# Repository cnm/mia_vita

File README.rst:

HOW TO BUILD MIA_VITA PROJECT
-----------------------------

*There is a very usefull Makefile at the top dir*

To compile the miavita project do this:

   - First download it from github
      $ git clone "https://github.com/cnm/mia_vita"

      (or if you are a developer)
      $ git clone "git@github.com:cnm/mia_vita"

   - Update the submodule (only necessary to run once)
      $ make init_git_submodules

   - Compile the ts7500_kernel ()
      $ make kernel

   - Compile all the code (except the kernel)
      $ make all

   - Install everything needed to the sdcard except the kernel

Overall help
------------

File Structure
==============

This is the file structure::

    .
    clean               - Directory for cleaning up the TS-7500 debian partition
    crosstool           - Crosstools binaries to compile for ARM
    documentation       - Documentation
    fred_framework      -
    interruption        - Module to treat the two interruptions
    kernel_sender       - Fred module which sends packets
    old_stuff           - Just for historical purposes. Should be deleted soon.
    rt2501              - Module changed to do the synchronization
    rt3070              - Module rt3070 for the wireless devices. It has not be changed.
    syscall             - Simple syscall to access the time set by the GPS
    timestamp-module    -
    ts7500ctl           - Binary of the ts7500ctl not changed. Just usefull to test big banging.
    ts7500_kernel       - Modified kernel for working in the TS7500

How to pull the git sub modules
===============================

* Pull the main module:
$> git clone "git@github.com:cnm/mia_vita.git"

* Optional check the status
$> git submodule status

* First add the submodule repository URLs to .git/config by running:
$> git submodule init

* Update the submodules
$> git submodules update

Development Username and password
=================================

*Arm devices*:

* Username: root
* Password: cnm

*Laptop*:

* Username: miavita
* password: inesc-id

FIRST STEPS - Connect to the RT7750 with serial cable
=====================================================

* Install minicom
* Run sudo minicom -s
* Set in Serial Port Setup

  * Serial Device: /dev/ttyUSB0 (or /dev/ttyUSB1)

  * Bps: 115200 8N1

  * Hardware Flow Control: No

Documentation URLs
==================
In here put the cites with documentation for the little arms:

* http://tech.groups.yahoo.com/group/ts-7000/

Sites to discover what chipset is in what wireless card

* http://wireless.kernel.org/en/users/Drivers/
* http://linux-wless.passys.nl/

Filesystem and kernels
======================
http://tagus.inesc-id.pt/~jtrindade/mia_vita/

Stable image is at:

http://tagus.inesc-id.pt/~jtrindade/mia_vita/block_images/mia_vita_image_stable

Establishing AD-HOC Communication (On the OLD devices with rt2050)
===================================================================

PC1 - LGs laptops from INESC
PC2 - TS-7550s

Run in PC1
##########
* ifconfig eth1 down
* ifconfig eth1 up
* iwconfig eth1 essid teste mode Ad-Hoc channel 1 ap 02:0c:f1:b5:8f:01 key off
* ifconfig eth1 192.168.0.1

Run in PC2
#########
* Edit the file /etc/modprobe.d/blacklist and add rt73usb
* Copy the file "rt73_ts7500.ko" to "/lib/modules/2.6.24.4/kernel/drivers/net/wireless/rt2x00". You may find the rt_ts7500.ko file in this zip file: "ftp://ftp.embeddedarm.com/ts-arm-sbc/ts-7500-linux/binaries/wifi-g-usb-2_rt2501usb-binaries.tar.gz"
* Run depmod -a
* Restart (don't really now if it is necessary)
* ifconfig rausbwifi up
* iwconfig rausbwifi essid teste mode Ad-Hoc channel 1 ap 02:0C:F1:B5:CC:5D key off
* ifconfig rausbwifi 192.168.0.25

Autostart interfaces in the TS7550
##################################
I added the following lines to /etc/network/interfaces:

auto rausbwifi
iface rausbwifi inet static
    address 192.168.0.25
    netmask 255.255.255.0
    pre-up /root/adhoc.sh

Note that the /root/adhoc.sh is a script with the previous instructions (don't forget to markit executable)

Placa Wireless IOGEAR (Can't make it work in adhoc)
====================================================

*Modulos:*
zd1211 -> Old module developed by the company (available in sourceforge)
zd1211rw -> New module developed by the community (available since 2.6.18-rc1)

*Referencias:*
Site of the module:
http://wiki.debian.org/zd1211rw

Site to compile the module + arguments of the iwconfig:
https://docs.google.com/viewer?url=http://www.linuxowl.com/ffs/DocsSoftware/SWMULZ-5400-Linux-UserGuide.pdf

Automatically boot into Debian linux
====================================
In linux initrd (busybox) in the root directory issue:

rm linuxrc; ln -sf linuxrc-sdroot linuxrc; save

Boot from sdcard via hardware
=============================

Connect pin 7 to GND

Changes done in the Operating System
====================================

Fix the name of the wireless card
---------------------------------
Add the file "01-our-rewrite.rules" to /etc/udev.d/rules with the following text:

   # All ralink wireless are named rausbwifi
   SUBSYSTEM=="net", ACTION=="add", KERNEL=="ra*", NAME="rausbwifi"

Blacklist the rt73 usb driver
-----------------------------
add "blacklist rt73usb" to /etc/modprobe.d/blacklist

Startup adhoc at the beggining
-------------------------------
In /etc/network/interfaces put:

    auto rausbwifi
    iface rausbwifi inet static
    address 192.168.0.3
    netmask 255.255.255.0
    pre-up /root/adhoc.sh rausbwifi 192.168.1.3

and /root/adhoc.sh should contain:

#!/bin/bash

    ifconfig $1 up
    iwconfig $1 mode managed
    sleep 3
    ifconfig $1 down
    ifconfig $1 up
    iwconfig $1 mode ad-hoc essid teste channel 1 ap 02:0C:F1:B5:CC:5D
    iwconfig $1 rate 1M
    ifconfig $1 $2

How to compile a user program in another machine for ts-7500
============================================================
* First setup the cross-compile. Download it from: ftp://ftp.embeddedarm.com/ts-arm-sbc/ts-7500-linux/cross-toolchains/crosstool-linux-gcc-4.2.1-glibc-2.7-oabi.tar.gz

* Untar it: tar xvzf crosstool-linux-gcc-4.2.1-glibc-2.7-oabi.tar.gz

* cd into usr/local/arm-oabi-toolchain/arm-unknown-linux-gnu/bin/

* Check if you have a broken link. In my case ``ls -l`` gives me this broken link: arm-unknown-linux-gnu-cc -> /usr/local/arm-oabi-toolchain/arm-unknown-linux-gnu/bin/arm-unknown-linux-gnu-gcc

* Fix it:

    $ rm arm-unknown-linux-gnu-cc

    $ ln -s \`pwd\`/arm-unknown-linux-gnu-gcc arm-unknown-linux-gnu-cc

* Now to compile programs for the ts-7500 just use ``arm-unknown-linux-gnu-gcc`` instead of ``gcc``

How to compile kernel for the TS-7500 node
==========================================

* Download the kernel from: ftp://ftp.embeddedarm.com/ts-arm-sbc/ts-7500-linux/sources/linux-2.6.24-ts-src-aug102009.tar.gz
 (or fetch it from: http://github.com/joninvski/ts_7500_kernel )

* Download the crosstool chain: ftp://ftp.embeddedarm.com/ts-arm-sbc/ts-7500-linux/cross-toolchains/crosstool-linux-gcc-4.2.1-glibc-2.7-oabi.tar.gz
 (or fetch it from: http://github.com/joninvski/arm-uclibc-3.4.6 )

* Download the module for the wireless card: ftp://ftp.embeddedarm.com/ts-arm-sbc/ts-7500-linux/sources/wifi-g-usb-2_rt2501usb-sources.tar.gz
 (or fetch it from: http://github.com/joninvski/USB_Wifi_RT2501_TS-7500 )

First compile the kernel
------------------------

* In the 2.6.24.4-cavium directory change the Makefile pointing it to the correct path. In my case:

  * CROSS_COMPILE   ?= /home/workspace/plaquinhas/kernel/arm-uclibc-3.4.6/bin/arm-linux-

* Put the crosstoll chain in the path

* Run: $> make ts7500_defconfig

* Run: $> make menuconfig
(If there is any error compiling menuconfig just install the package libncurses-dev)

* Go to networking and select all the modules necessary for iptables/netfilter
(The .config present in the git repository contains this information)

* Run: $> make modules; make modules_install
(in here i did a litlle trick: chmod a+w /lib/modules to be able to install modules whitout being root)

Copy the kernel to the sd card
------------------------------

* Put the sdcard in the computer (let's assume sdb)

* Run: dd if=arch/arm/boot/zImage of=/dev/sdb2\

* Mount /dev/sdb4

* Copy the modules present in /lib/modules/2.6.24.4/ to the card 4th partition (to the same directory)

Compile the usb wifi card driver
--------------------------------

* Go the the directory of the usb wifi source code.

* In the Makefile change the cross tools path and the target to 7500
(you can find these changes in the git repository)

* make

* Copy the ts73.ko file to the /lib/modules/2.6.24.4/kernel/drivers/net/wireless/rt2x00/rt73_ts7500.ko (note this is in the forth partition of the sd-card)o

* You should probably (not tested) run depmod on the arm node (then restart)

Run the kernel from the sd-card
-------------------------------

* Put the jumpers in the development board: JP1 = ON; JP2 = OFF

* Do a depmod -a to do all module dependencies

Copy the kernel and initrd to the flash in the arm
--------------------------------------------------

* On my pc (I cannot to this in the card) I copy the sdb2 and sdb3 partitions to two files and then use those files to copy to the flash. This is how to do it.

* Put the sd-card on the pc

* dd if=/dev/nbd2 of=/tmp/zImage
* dd if=/dev/nbd3 of=/tmp/initrd
* Copy both these files to the /dev/ndb4 file system (mount it!!!!!!)
* Unmount /dev/ndb4 after copy
* Put the sd-card on the arm and then turn it up
* Do:
 * spiflashctl -W 4095 -z 512 -k part1 -i /temp/zImage
 * spiflashctl -W 32 -z 65536 -k part2 -i /temp/initrd
 * sync

Add a batman service at startup
==============================
* update-rc.d batman-adv defaults

Udev rule
=========

On some linux distros users experience some minicom problems, while using the serial cable to connect to the development board. In other words, minicom stops working wtih an error message similar to::

   Unable to open /dev/ttyUSB0

This happens because the kernel keeps changing the device name and ttyUSB0 is now ttyUSB1. This can be avoided by creating an udev rule. The following udev rule is the simplest one, which provides a workaround to this problem:

* Open file /etc/udev/rules.d/99_serial_cable.rules
* Write: SUBSYSTEM=="usb", KERNEL=="ttyUSB*", NAME="ttyUSB0"

Or you can just copy and execute the command::

   sudo sh -c 'echo "SUBSYSTEM==\"usb\", KERNEL==\"ttyUSB*\", NAME=\"ttyUSB0\"" > /etc/udev/rules.d/99_serial_cable.rules'

You will need to restar udev or your pc.

Keep in mind that this rule is very simple and it only tells the udev layer to give the name ttyUSB0 to every device that the kernel reports as beginning with ttyUSB. If you ever need to connect two serial cables via USB adapters, you'll need to add another parameter to the rule above. To do this we first need the device ID for each usb adapter. Issue::

   lsusb

Which should give you an output similar to::

   Bus 005 Device 001: ID 1d6b:0001 Linux Foundation 1.1 root hub
   Bus 004 Device 002: ID 0b05:1712 ASUSTek Computer, Inc. BT-183 Bluetooth 2.0+EDR adapter
   Bus 004 Device 001: ID 1d6b:0001 Linux Foundation 1.1 root hub
   Bus 003 Device 002: ID 04f3:0210 Elan Microelectronics Corp. AM-400 Hama Optical Mouse

Now, what we're looking for is the device id, which is the second hexadecimal number in the ID field. For example, the blue tooth adapter has a device ID of 1712.

The udev rule for multiple adapters becomes::

   SUBSYSTEM=="usb", ATTR{idProduct}=="0001", NAME="ttyUSB0"
   SUBSYSTEM=="usb", ATTR{idProduct}=="0002", NAME="ttyUSB1"

The udev will give the name ttyUSB0 to the usb adapter with id 0001 and ttyUSB1 to the usb adapter with id 0002.

Compile spictl
==============

Erase the LD_FLAGS variable from the Makefile

Update the FPGA
===============

Get the new FPGA from::

    wget ftp://ftp.embeddedarm.com/ts-arm-sbc/ts-7500-linux/binaries/ts-bitstreams/ts7500_opencore-rev5-8XUART.vme.gz

Compile the ts7500ctl tool::

    wget ftp://ftp.embeddedarm.com/ts-arm-sbc/ts-7500-linux/sources/ts7500ctl.c
    wget ftp://ftp.embeddedarm.com/ts-arm-sbc/ts-7500-linux/sources/vmopcode.h
    wget ftp://ftp.embeddedarm.com/ts-arm-sbc/ts-7500-linux/sources/ispvm.c
    gcc -Wall -O -o ts7500ctl ts7500ctl.c ispvm.c

Load the new FPGA::

    ./ts7500ctl -l ts7500_opencore-rev5-8XUART.vme.gz

Test::

    arm3:~# ./spictl -l 1 -w 0B:00:20:00:00 -r 32 | hexdump -C
    00000000  20 94 e0 d4 30 03 e0 07  60 07 e0 64 00 08 e0 07  | ...0...`..d....|
    00000010  a0 03 e0 83 74 37 e0 a0  00 10 23 00 13 40 9f e4  |....t7....#..@..|

How to add a system call on arm
===============================

Adding a system call is not as straight forward as creating a kernel module. The issue is that the system call table is a static table that resides inside
the kernel. Therefore it cannot be modified dynamically. More specifically you can modify the table but it is impossible to extend it. As a result, adding
a system call requires recompiling the kernel itself.

First thing first, download the kernel sources for the ts7500 board. cd into the downloaded sources and lets begin.
Adding a system call can be done in four steps:

* Edit the file ``arch/arm/kernel/calls.S`` and add a ``CALL`` statement::

    CALL(sys_mycall)

  Note: The syscall will be called ``mycall``, but here it is necessary to
  prefix it with ``sys``. Another thing to consider is that the system call
  table size must be a multiple of 4. For example if it has 352 calls you
  need to add 4 more calls. Use ``CALL(sys_ni_syscall)`` to add dummy system
  calls. When you're finished take note of your system call number, in our
  case we added 4 calls and suppose that our call is the last one, its number
  will be 356.

* Edit the file ``include/asm/unistd.h`` and add a ``define`` statement to the ones already in there::

    #define __NR_mycall       (__NR_SYSCALL_BASE+356)

  Note: The define constant must be prefixed with ``__NR_`` and notice the
  number 356.

* Create your system call. You'll need to decide which folder to put your .c file. There are a lot of choices here - fd, ipc, drivers, etc. No matter where you decide to put it you'll need to change the Makefile in it to compile your file. Suppose your file is named ``mysyscall.c``, add ``mysyscall.o`` to one of the object targets in the Makefile. Make sure that target will run, that is, if that option is enabled in the kernel. The ``mysyscall.c`` file will look something like::

    #include <linux/linkage.h>
    #include <linux/kernel.h>

    asmlinkage int sys_mysyscall(void){
     printk(KERN_EMERG "MY SYSCALL\n");
     return 1;
    }

* Finally, edit the file ``include/linux/syscalls.h`` and add your call header::

    asmlinkage int sys_mysyscall(void);

Mac Addresses
=============

Ethernet
########

    MV-47 - 00:d0:69:43:3f:ce - 99

    MV-34 - 00:d0:69:43:3f:c0 - 109

    MV-58 - 00:d0:69:43:3f:b9 - 145

    MV-50 - 00:d0:69:43:3f:c7 - 138

    MV-49 - 00:d0:69:43:3f:b3 - 143

Wireless cards
##############

    MV-61 94:0c:6d:e1:85:e5

    MV-41 e0:cb:4e:a6:5a:be

    Simao 94:44:52:01:95:b3

Setting up kthread to send data
===============================

The kthread module resides inside ``kernel_sender`` folder and has several parameters which can be useful to configure it::

    # modinfo send_kthread.ko

    filename:       sender_kthread.ko
    description:    This module spawns a thread which reads the buffer exported by João ands sends samples accross the network.
    author:         Frederico Gonçalves, [frederico.lopes.goncalves@gmail.com]
    license:        GPL v2
    depends:        int_mod
    vermagic:       2.6.24.4 mod_unload ARMv4
    parm:           bind_ip:This is the ip which the kernel thread will bind to. Default is localhost. (charp)
    parm:           sink_ip:This is the sink ip. Default is localhost. (charp)
    parm:           sport:This is the UDP port which the sender thread will bind to. Default is 57843. (ushort)
    parm:           sink_port:This is the sink UDP port. Default is 57843. (ushort)
    parm:           node_id:This is the identifier of the node running this thread. Defaults to 0. (ushort)
    parm:           read_t:The sleep time for reading the buffer. (uint)

Every parameter has its own default value, but you'll probably want to specify ``bind_ip`` and ``sink_ip`` ::

    # insmod sender_kthread.ko bind-ip="172.20.41.138" sink-ip="172.20.41.123"

Don't forget to insert the ``int_mod.c`` module first and that's it. You'll just need to run the server program as ::

    # user/main

You can specify aditional parameters ::

    # user/main -h

    Usage: ./main [-i <interface>] [-p <listen_on_port>] [-b <output_binary_file>] [-j <output_json_file>]
    -i     Interface name on which the program will listen. Default is eth0
    -p     UDP port on which the program will listen. Default is 57843
    -b     Name of the binary file to where the data is going to be written. Default is miavita.bin
    -j     Name of the json file to where the data is going to be written. Default is miavita.json

Test Results (made by Simao)
============================

Check the following url:

http://tagus.inesc-id.pt/~spedro/MIA-VITA/

Test Image (made by Simao)
============================

This image should be used for all wireless tests from now on.

check the following url:
http://tagus.inesc-id.pt/~spedro/mia_vita_image_tests_0.1

Arms Embedded suggested this Wireless card with external antenna
================================================================

HAWNU1 Hi-Gain Wireless-150N USB Network Adapter w/Range Amplifi
http://www.gohawking.com/store/product_info.php?products_id=438&osCsid=valhhlsf19rnueqs8shgdgduk1

Compile for uCLIBC
==================

Use the crosstool/arm-uclibc-3.4.6/ not the crosstool/arm-unknown-linux-gnu/ crosstool

Ping broadcast in ADHOC
=======================

    echo "0" > /proc/sys/net/ipv4/icmp_echo_ignore_broadcasts

Change from 802.11N to 802.11B
===============================

Edit file:

    etc/Wireless/RT2870STA/RT2870STA.dat

and change WirelessMode=5 to WirelessMode=1

More info available at: http://ubuntuforums.org/showthread.php?t=1566572

    @> WirelessMode=value
        0: legacy 11b/g mixed
        1: legacy 11B only
        2: legacy 11A only //Not support in RfIcType=1(id=RFIC_5225) and RfIcType=2(id=RFIC_5325)
        3: legacy 11a/b/g mixed //Not support in RfIcType=1(id=RFIC_5225) and RfIcType=2(id=RFIC_5325)
        4: legacy 11G only
        5: 11ABGN mixed
        6: 11N only
        7: 11GN mixed
        8: 11AN mixed
        9: 11BGN mixed
        10: 11AGN mixed

Some test commands
==================

Commands ::

   insmod int_mod.ko
   insmod sender_kthread.ko bind-ip="192.168.2.45" sink-ip="192.168.2.47" node-id="5"
   ./receiver -i bat0 -j /tmp/manel/miavita.json -z /tmp/manel/miavita.json.archive

================================

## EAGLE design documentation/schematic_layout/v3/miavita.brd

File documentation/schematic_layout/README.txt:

FILE *.brd -> Circuit Board layout
FILE *.sch -> Circuit Schematic

IMPORTANT:
The pdf's exports sould be done in a way so they face each other.

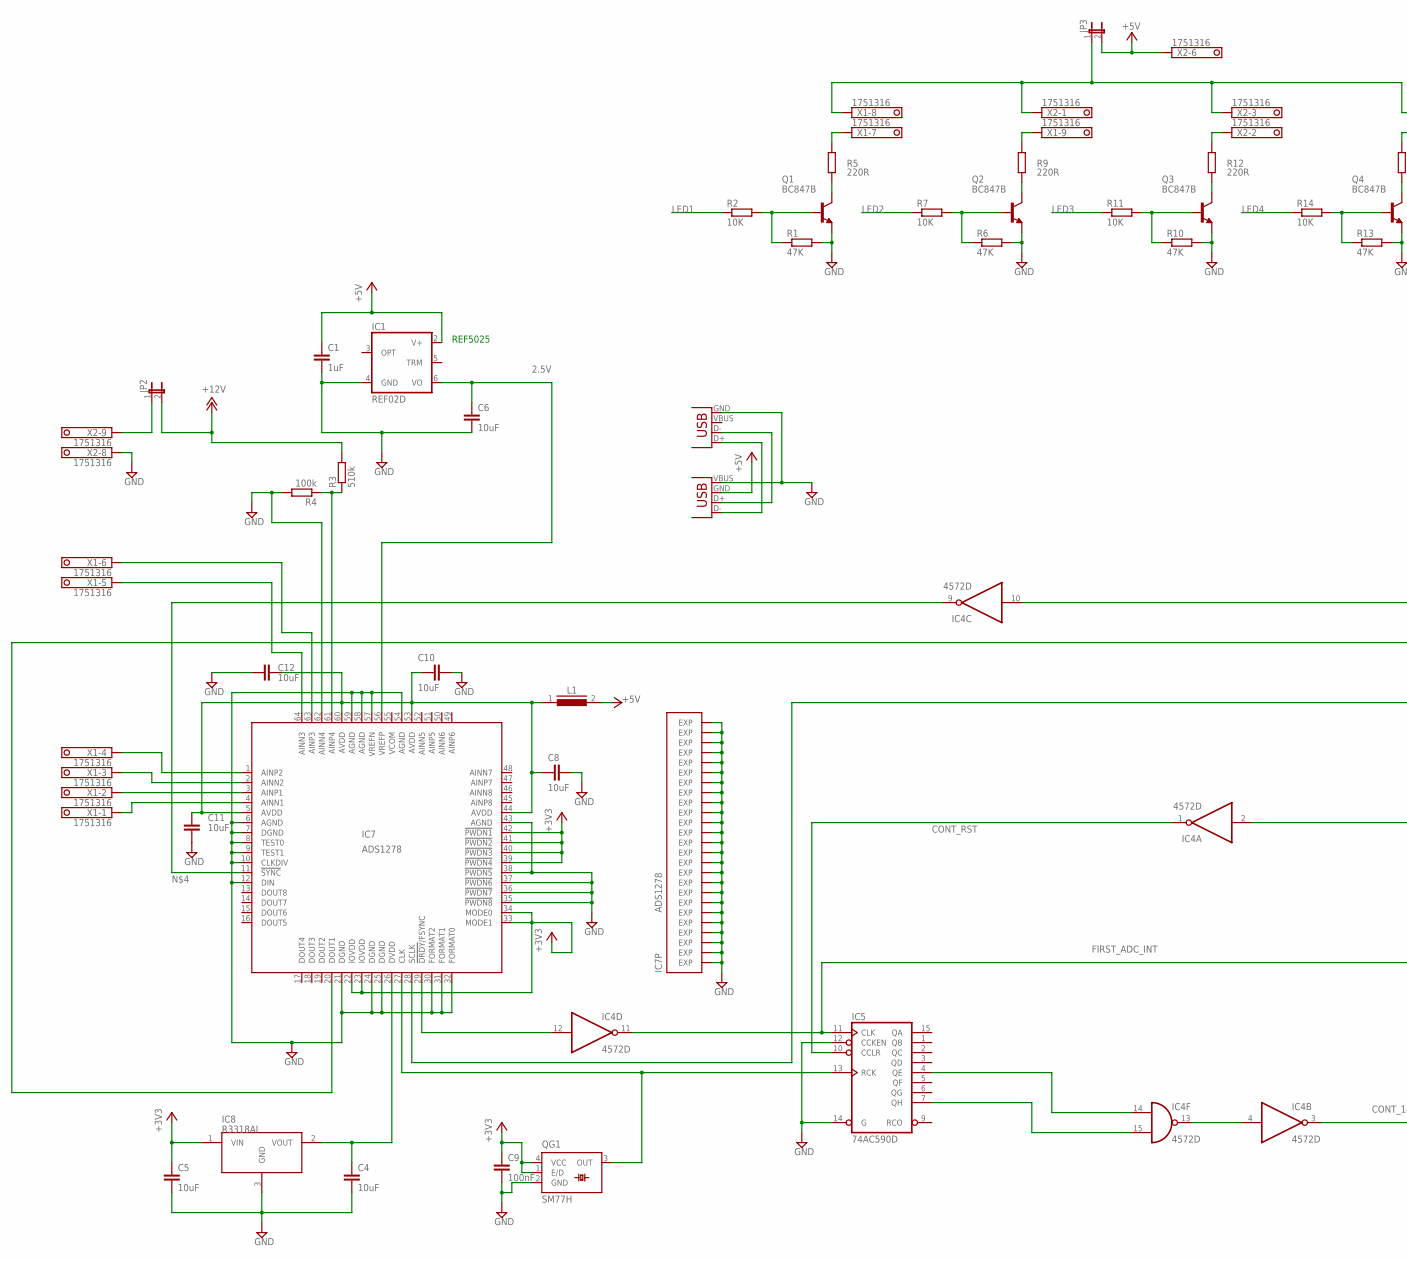
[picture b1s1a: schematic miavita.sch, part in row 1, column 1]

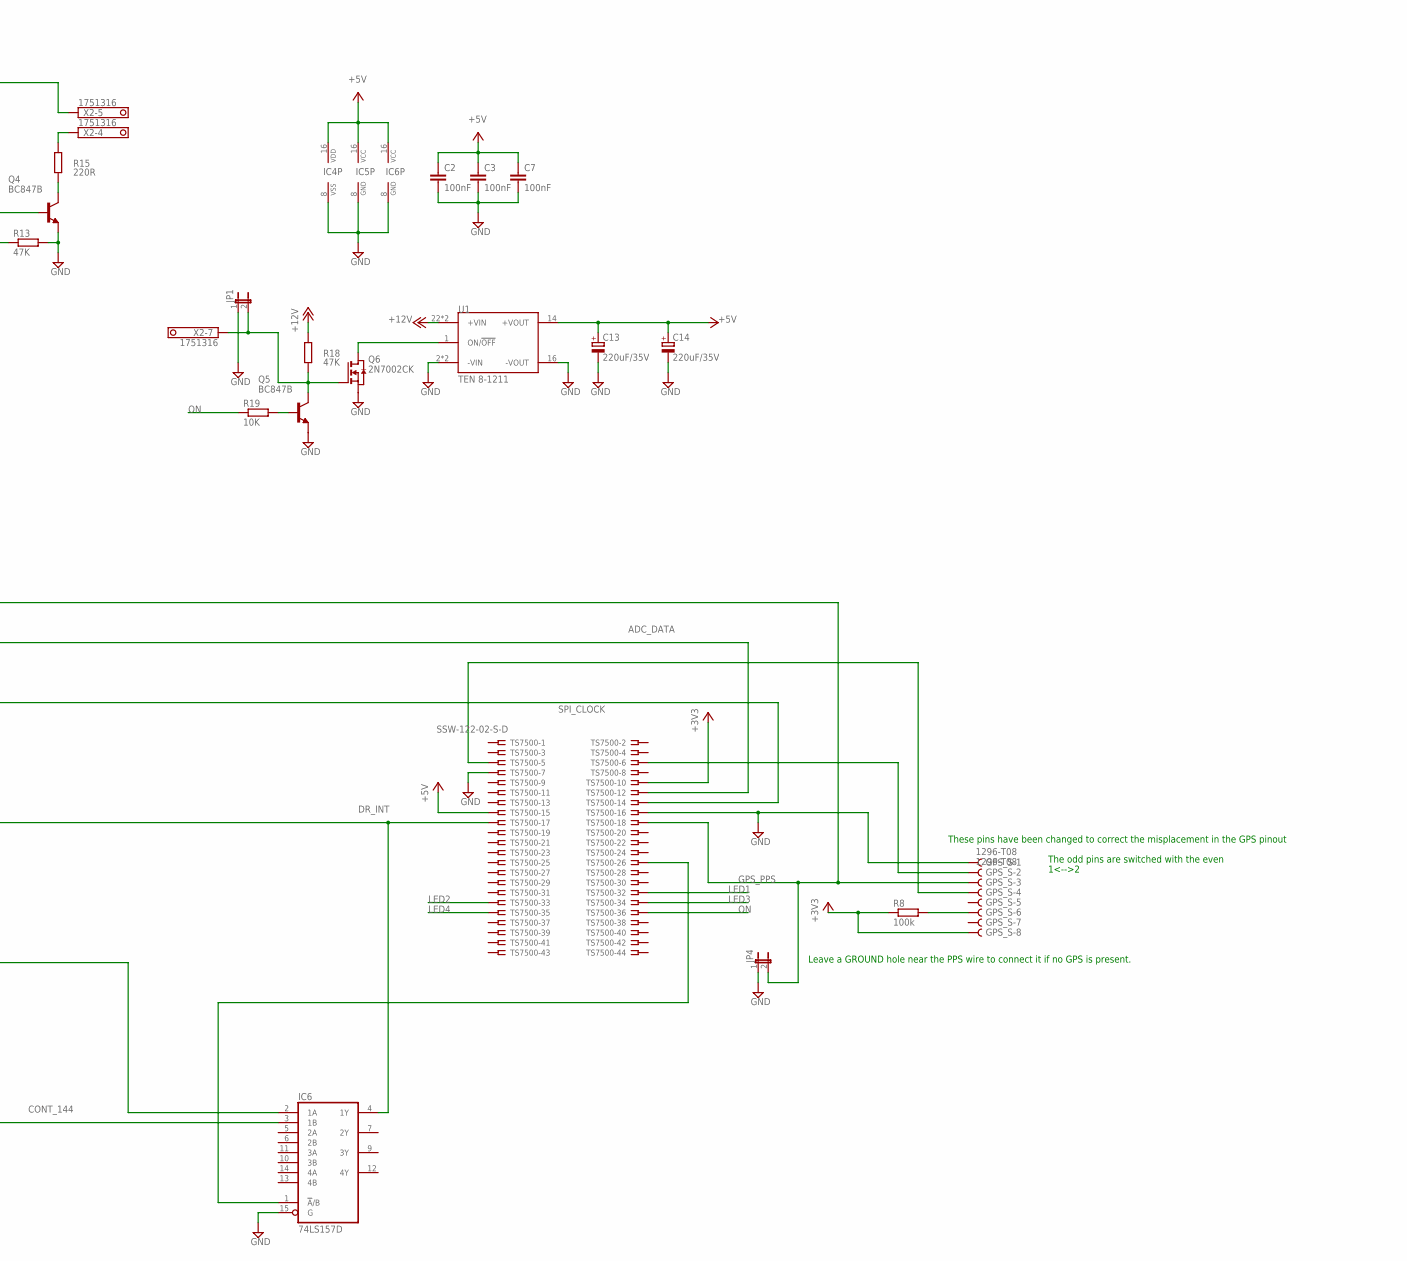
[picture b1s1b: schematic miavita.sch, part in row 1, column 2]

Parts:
C1: 1uF; C0603
C2, C3, C7, C9: 100nF; C0603
C4, C5, C6: 10uF; C1210
C8, C10, C11, C12: 10uF; C0805
C13, C14: 220uF/35V; UD-10X10_NICHICON
GPS_S: 1296-T08; 1296-08
IC1: REF02D; SO08
IC4: 4572D; SO16
IC5: 74AC590D; SO16
IC6: 74LS157D; SO16
IC7: ADS1278; HTQFP-64-PAP
IC8: R3318AI; SOT23
JP1, JP2, JP3, JP4: JP1E; JP1
L1: FAIR-RITE_2506031027Y0; L0603
Q1, Q2, Q3, Q4, Q5: BC847B; SOT23
Q6: 2N7002CK; SOT23
QG1: SM77H
R1, R6, R10, R13, R18: 47K; R0603
R2, R7, R11, R14, R19: 10K; R0603
R3: 510k; R0603
R4, R8: 100k; R0603
R5, R9, R12, R15: 220R; R0603
TS7500: SSW-122-02-S-D
U1: TEN 8-1211; TRACOPOWER_TEN-8-SERIES
USBA: USB-A-H
USBB: USBPTH; USB-B-PTH
X1, X2: 1751316

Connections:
2.5V: C6.1, IC1.6 (VO), IC7.56 (VREFP)
+1V8: C4.1, IC7.26 (DVDD), IC8.2 (VOUT)
+3V3: C5.1, C9.1, GPS_S.8, IC7.22 (IOVDD), IC7.23 (IOVDD), IC7.33 (MODE1), IC7.34 (MODE0), IC7.39 (!PWDN4), IC7.40 (!PWDN3), IC7.41 (!PWDN2), IC7.42 (!PWDN1), IC8.1 (VIN), QG1.1 (E/D), QG1.4 (VCC), R8.1, TS7500.10
+5V: C1.1, C2.1, C3.1, C7.1, C13.+, C14.+, IC1.2 (V+), IC4.16 (VDD), IC5.16 (VCC), IC6.16 (VCC), JP3.2, L1.2, TS7500.15, U1.14 (+VOUT), USBA.GND (VBUS), X2.6
+12V: JP2.2, R3.2, R18.1, U1.22 (+VIN), U1.23 (+VIN)
ADC_DATA: IC7.20 (DOUT1), TS7500.12
CONT_144: IC4.3 (O), IC6.3 (1B)
CONT_RST: IC4.1 (O), IC5.10 (CCLR)
DR_INT: IC4.2 (I), IC6.4 (1Y), TS7500.17
FIRST_ADC_INT: IC4.11 (O), IC5.11 (CLK), IC6.2 (1A)
GND: C1.2, C2.2, C3.2, C4.2, C5.2, C6.2, C7.2, C8.2, C9.2, C10.2, C11.2, C12.2, C13.-, C14.-, GPS_S.1, IC1.4 (GND), IC4.8 (VSS), IC5.8 (GND), IC5.12 (CCKEN), IC5.14 (G), IC6.8 (GND), IC6.15 (G), IC7.6 (AGND), IC7.7 (DGND), IC7.8 (TEST0), IC7.9 (TEST1), IC7.10 (CLKDIV), IC7.12 (DIN), IC7.21 (DGND), IC7.24 (DGND), IC7.25 (DGND), IC7.30 (FORMAT2), IC7.31 (FORMAT1), IC7.32 (FORMAT0), IC7.35 (!PWDN8), IC7.36 (!PWDN7), IC7.37 (!PWDN6), IC7.38 (!PWDN5), IC7.43 (AGND), IC7.54 (AGND), IC7.57 (VREFN), IC7.58 (AGND), IC7.59 (AGND), IC7.62 (AINN4), IC7.EXP1 (EXP), IC7.EXP2 (EXP), IC7.EXP3 (EXP), IC7.EXP4 (EXP), IC7.EXP5 (EXP), IC7.EXP6 (EXP), IC7.EXP7 (EXP), IC7.EXP8 (EXP), IC7.EXP9 (EXP), IC7.EXP10 (EXP), IC7.EXP11 (EXP), IC7.EXP12 (EXP), IC7.EXP13 (EXP), IC7.EXP14 (EXP), IC7.EXP15 (EXP), IC7.EXP16 (EXP), IC7.EXP17 (EXP), IC7.EXP18 (EXP), IC7.EXP19 (EXP), IC7.EXP20 (EXP), IC7.EXP21 (EXP), IC7.EXP22 (EXP), IC7.EXP23 (EXP), IC7.EXP24 (EXP), IC7.EXP25 (EXP), IC8.3 (GND), JP1.1, JP4.1, Q1.2 (E), Q2.2 (E), Q3.2 (E), Q4.2 (E), Q5.2 (E), Q6.2 (S), QG1.2 (GND), R1.2, R4.2, R6.2, R10.2, R13.2, TS7500.7, TS7500.16, U1.2 (-VIN), U1.3 (-VIN), U1.16 (-VOUT), USBA.VBUS (GND), USBB.GND, X2.8
GPS_PPS: GPS_S.3, IC4.10 (I), JP4.2, TS7500.18
LED1: R2.1, TS7500.32
LED2: R7.1, TS7500.33
LED3: R11.1, TS7500.34
LED4: R14.1, TS7500.35
unnamed: IC6.1 (!A!/B), TS7500.26
unnamed: IC4.15 (I1), IC5.7 (QH)
unnamed: IC4.14 (I0), IC5.4 (QE)
unnamed: IC4.9 (O), IC7.11 (!SYNC)
unnamed: IC4.4 (I), IC4.13 (O)
unnamed: IC4.12 (I), IC7.29 (!DRDY!/FSYNC)
unnamed: IC7.3 (AINP1), X1.2
unnamed: Q5.1 (B), R19.2
unnamed: IC7.4 (AINN1), X1.1
unnamed: IC7.1 (AINP2), X1.4
unnamed: IC7.61 (AINP4), R3.1, R4.1
unnamed: USBA.D+ (D-), USBB.D-
unnamed: IC7.63 (AINP3), X1.6
unnamed: Q2.1 (B), R6.1, R7.2
unnamed: Q2.3 (C), R9.1
unnamed: IC5.13 (RCK), IC7.27 (CLK), QG1.3 (OUT)
unnamed: USBA.D- (D+), USBB.D+
unnamed: C8.1, C10.1, C11.1, C12.1, IC7.5 (AVDD), IC7.44 (AVDD), IC7.53 (AVDD), IC7.60 (AVDD), L1.1
unnamed: R9.2, X1.9
unnamed: Q3.1 (B), R10.1, R11.2
unnamed: Q3.3 (C), R12.1
unnamed: R12.2, X2.2
unnamed: Q4.1 (B), R13.1, R14.2
unnamed: Q4.3 (C), R15.1
unnamed: R15.2, X2.4
unnamed: JP2.1, X2.9
unnamed: JP3.1, X1.8, X2.1, X2.3, X2.5
unnamed: IC7.2 (AINN2), X1.3
unnamed: JP1.2, Q5.3 (C), Q6.1 (G), R18.2, X2.7
unnamed: Q6.3 (D), U1.1 (ON/!OFF)
unnamed: IC7.64 (AINN3), X1.5
unnamed: Q1.3 (C), R5.1
unnamed: Q1.1 (B), R1.1, R2.2
unnamed: R5.2, X1.7
unnamed: GPS_S.2, TS7500.6
unnamed: GPS_S.4, TS7500.5
unnamed: GPS_S.6, R8.2
ON: R19.1, TS7500.36
SPI_CLOCK: IC7.28 (SCLK), TS7500.14

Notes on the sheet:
Leave a GROUND hole near the PPS wire to connect it if no GPS is present.
REF5025
These pins have been changed to correct the misplacement in the GPS pinout
The odd pins are switched with the even
1<-->2

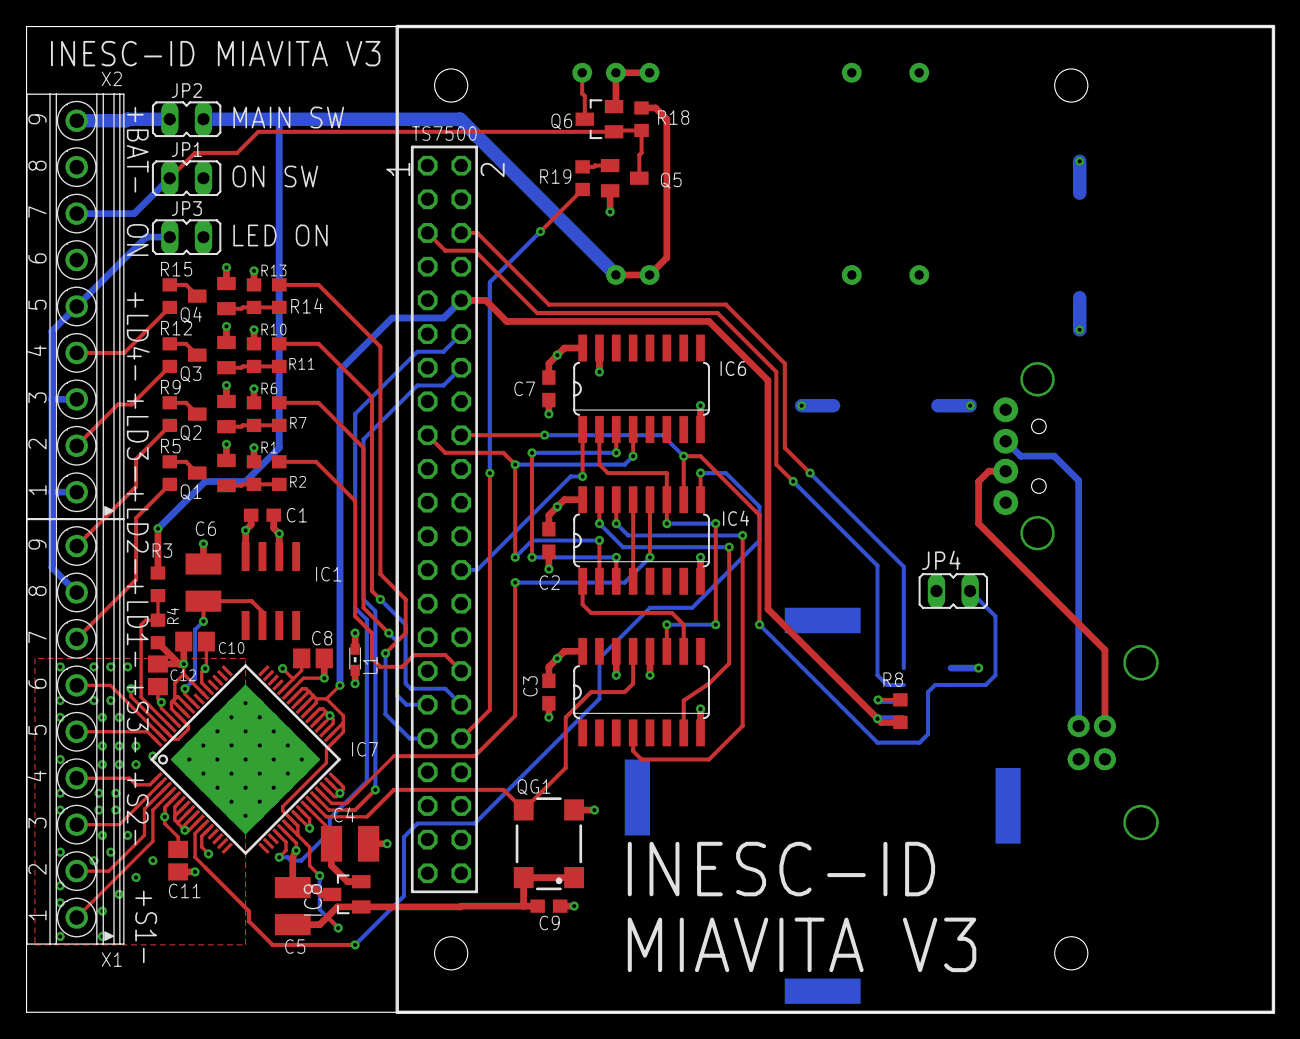
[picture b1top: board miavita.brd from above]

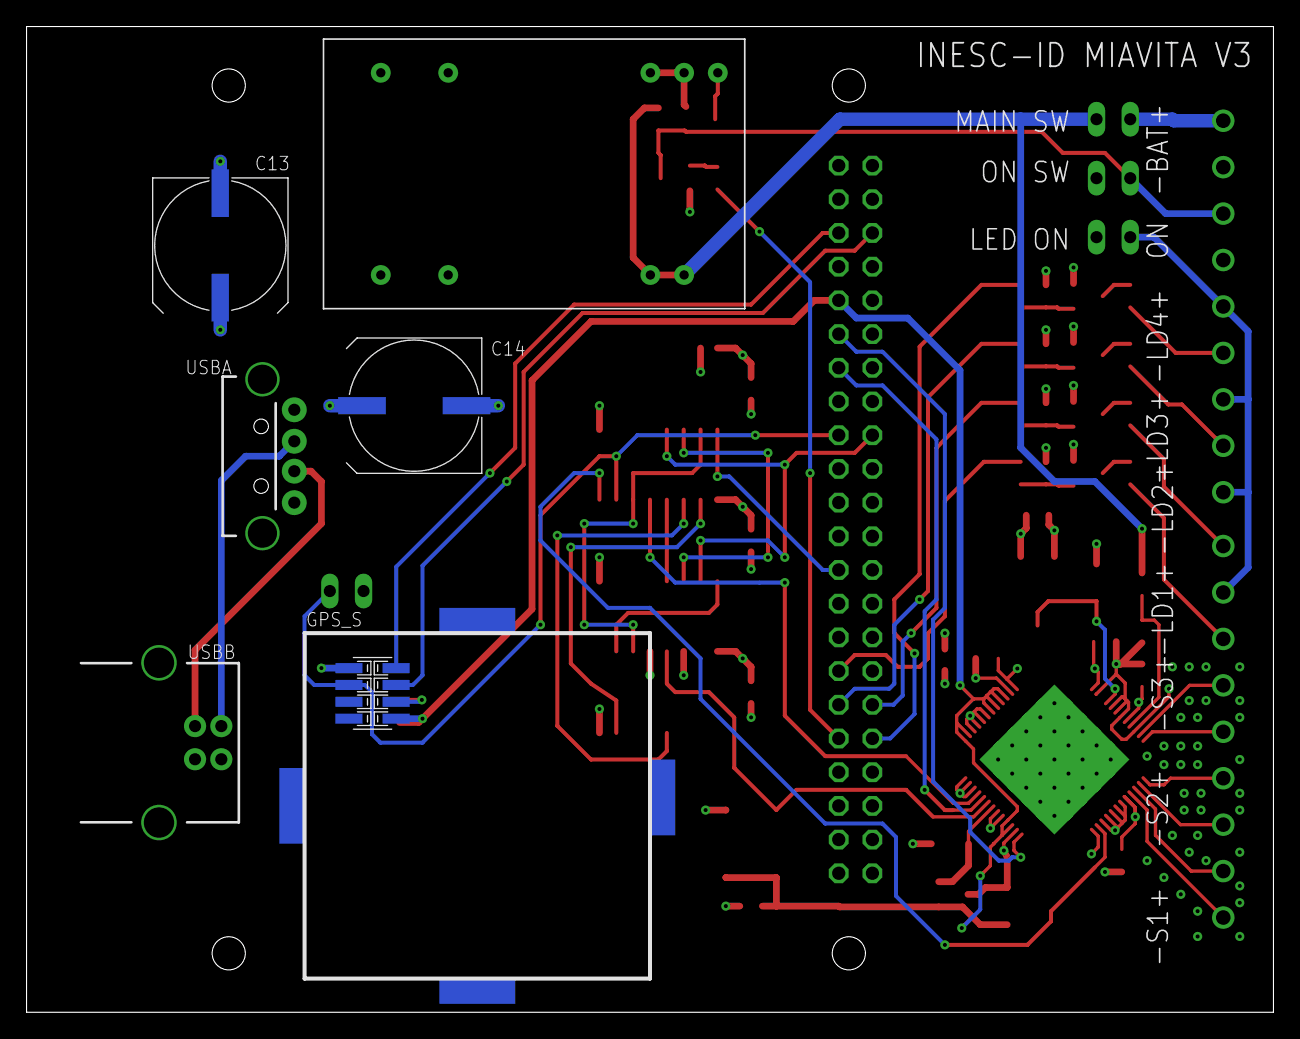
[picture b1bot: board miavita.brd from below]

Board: 4 copper layers, 94.0 x 74.3 mm, 56 parts (6 on the bottom side), 55 nets.

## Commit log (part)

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2011-12-26 mais alguns toques na desagregação
2011-12-26 deaggregation complete. Going to compile in other pc
2011-12-26 Finalmente tenho a framework a compilar. Falta testar.
2011-12-27 Cleaning up things
2011-12-27 Added a git ignore
2011-12-27 Added more documentation
2011-12-27 FIx2?
2011-12-27 Added the crosstool
2011-12-27 Doc and symbolic links
2011-12-27 Ja sei qual é o problema, mas tenho de ir para casa.
2011-12-27 Ok o problema tem haver com implementação, mas é corrigivel em runtime. Necessito de explicar isto no manual e ainda testar.
2011-12-29 Já descobri um dos bugs. Só que agora n consigo reinjectar o pacote na rede. Erro 90
2011-12-29 Small fix on the README
2011-12-29 Small fix
2011-12-29 More doc
2011-12-29 More documentation
2011-12-29 Starting readme for rt2501
2011-12-29 Added instruction on where to download the rt2501 driver
2011-12-29 Aformatted
2011-12-29 Added documentation for the rt2501 (more detail)
2011-12-29 Update doc
2011-12-29 A agregação ao nível da aplkicação já funciona. Falta-me fazer uma thread que de x em x tempos envia dados.
2011-12-30 UPdated doc
2011-12-30 Removed timestamp-module subproject
2011-12-30 Network aggregation working. Need to add thread to aggregation to flush buffers.
2011-12-30 Starting to document fred_framework
2011-12-30 Added some more README info
2011-12-30 Adicionei um header à consuela porque n compilava para o ARM
2011-12-30 A consuela já funciona. Vou documentar a agregação. O que ainda não está feito: bug no quicksort e adaptar o driver rt2501 para suportar agregação.
2011-12-30 some codumentation
2012-01-05 Esquema: ficheiro fonte e png
2012-01-10 Atualizacao do esquema
2012-01-11 Adicionado o circuito da bateria
2012-01-23 Added step by step example
2012-02-01 Author: Fred. Acabei a documentação em pdf.
2012-02-06 Added board layout
2012-02-06 Changed layout and updated schematic
2012-02-07 Updated schematic and added new board layout
2012-02-09 Rewritten userland reader and corrected a bug in proc_entry.c
2012-02-09 Updated board layout
2012-02-13 Added 2\'s complement
2012-02-24 Added a few notes on the board layout
2012-02-24 Added top and bottom layer pdf and gerber file
2012-03-05 Created new board layout and renamed it
2012-04-30 Started README
2012-04-30 More doc for userland reader
2012-05-04 Some update to the documentation
2012-05-14 Added a README and changed directory structure
2012-05-14 Fixed directory structure README
2012-05-14 Now with makefiles that work in the arm
2012-05-14 Add version to xuartctl
2012-05-17 Change makefile with relative paths
2012-05-22 Clean
2012-05-22 Fixed
2012-05-22 Added more stuff to the readme
2012-05-22 Added some documentation
2012-05-28 UPdate Readme for interruption
2012-05-28 Added a read dio 26
2012-05-28 Added a variable as volatile
2012-05-29 Added small comment
2012-05-30 Corrected a bug in userland reader.
2012-05-30 Added datasheet for the adc
2012-06-01 Added README
2012-06-01 Added readme to button dir
2012-06-01 Added GPS utilities
2012-06-01 Added small README (again)
2012-06-01 Added GPS time once again
2012-06-01 Added instructions
2012-06-05 Added simple cluanup script
2012-06-05 Added gitignores
2012-06-12 Cleaned the schematic folder and updated the schematic to correct discovered problems
2012-06-15 Added electrical schematic
2012-06-20 Added fred doc
2012-06-20 Added a todo translate to kernel sender README
2012-06-20 Added gitignore to fred framework
2012-06-21 Removed unused variable for fpga
2012-06-21 Continue to making relative paths
2012-06-21 Updated ts7500_kernel
2012-06-21 Added proc_entry debug option
2012-06-21 Indented and changed debug flag
2012-06-21 Changed debug flag
2012-06-21 More indent
2012-06-22 Added parameters for kernel sender user program (the receiver)
2012-06-22 Idented list.c
2012-06-22 Kernel receiver ;) is now compiling with correct gcc (crosstool)
2012-06-22 Removed a warning
2012-06-22 Changed the port and now all work
2012-06-25 Idented sender thread
2012-06-25 Printing cleanup and old code cleanup
2012-06-25 Addded debug print in kernel sender
2012-06-25 Added DEBUG ifdef around printf in kernel receiver ;)
2012-06-25 Added debug lines to fpga
2012-06-25 Added two's complement
2012-06-26 Corrected the byte order.
2012-06-26 Minor cleanup
2012-06-26 Cleaned proc entry. Now dealing with samples
2012-06-26 Finished new proc entry read samples
2012-06-26 Simplified list
2012-06-26 Ready for the final test
2012-06-27 Added path if i want to remove GPS code later
2012-06-28 Added tags to gitignore
2012-06-28 More gitignore
2012-06-28 Renamed from duarte to visualization
2012-07-03 Changes in schematic (not complete)
2012-07-03 Corrected errors found in the prototype -- Final Layout (?)
2012-07-04 Possible changes to the schematic
2012-07-04 Generated the Gerber files for the final layout
2012-07-05 Tests stuff
2012-07-11 Corrected a bug and added debug prettier (intermediate)
2012-07-11 Deleted files mistakedly added in last commit
2012-07-11 Added a script simplify the GPS time test
2012-07-18 Added drawing explaining gps time
2012-07-18 Corrected default value
2012-07-18 Added README for Duarte visualization tool
2012-07-18 Updated visualization README
2012-07-18 Updated latest Duarte changes
2012-07-18 Trying to get Duarte latest version from dropbox
2012-07-19 Changed error in the Interruption-Makefile
2012-07-20 Updated the schematic to not be rotated
2012-07-20 Visualisation: Now Refreshing page is possible with f5
2012-07-23 Removed warning of undefined function from kernel sender
2012-07-23 Cleaning symvers
2012-07-23 Removed option that I've added for simao
2012-07-25 Revert "Changed the sample timestamping code"
    This reverts commit f82d23e7075e3d0cc465b59041e778d15ddb29a4.
2012-07-26 Corrected some errors in the JSON generation
2012-07-27 Updated receiver/README.rst
2012-07-27 Updated several README's
2012-08-14 Removed visualization
2012-08-14 Added submodule as ./visualization
2012-08-29 Moved v1 and added v2
2012-08-29 Moved the v2 directory (error last commit)
2012-08-29 Added Manual for V2
2012-09-04 Now with retries (latency)
2012-09-04 Now with dropped packets
2012-09-04 Corrected errors on left
2012-09-05 Files are now of 500 samples and corrected error on archive
2012-09-05 Ricardo fixes for the GPS
2012-09-08 Lots of stuff
2012-09-08 Read GPS
2012-09-08 Fixes on number node and new read_gps
2012-10-25 Added cover of the hardware node to the repo
2013-01-07 Quickly added pyplot script
2013-01-08 Several fixes in plotting
2013-01-09 Now writing temp files for each node and then moving them when they are complete
2013-01-09 Now using differente files for different nodes
2013-01-09 Changed y size and x size
2013-01-09 Generated json is now smaller
2013-01-09 More
2013-01-10 Plot with a lot of cleanup
2013-01-10 Outliers are being detected
2013-01-10 Outliers treatted (not pretty)
2013-01-10 Nice graphics
2013-01-11 Added two scripts created by simao to connect to adhoc and batman
2013-01-14 Update to miavita adhoc connection script
2013-01-14 Making graphs nicer
2013-01-14 Final fixes
2013-01-14 Reverted last commit
2013-01-15 This was what went for the presentation.
    And it was good....
2013-02-05 Update submodules
2013-02-05 Just some comments
2013-02-05 Forgot to end a comment
2013-02-05 Added arm scripts
2013-02-06 Fixed something wrong with parse argues on init counter
2013-02-06 Removed whitespaces at the end of file
2013-02-06 Stdout and stderr redirection fixed
2013-02-06 Now **only** corrected a bug in the set seconds syscall
2013-02-06 Added lines to truncate/append
2013-02-06 Blocked GPS acquiring and only then start collecting samples
2013-02-06 Added Makefile for all the project
2013-02-07 Test using usec from kernel
2013-02-08 Added Sesimbra Tests
2013-02-08 Finnaly removed the terrifying __GPS__ flag
2013-02-11 Added 'theirs' test in Sesimbra
2013-02-14 Small cleanups in interruption module
2013-02-14 Small cleanup in gps time
2013-04-05 Added mseed reader
2013-04-05 Moved resultsReader project
2013-04-05 Updated gitignore
2013-04-05 Cleaned up a little bit the java code
2013-04-05 Data is now ordered
2013-04-05 Added out.data file
2013-04-05 Update to pom
2013-04-08 Added all options
2013-04-08 Now depedendent jars are in maven repo
2013-04-08 Added options printing
2013-04-08 Small cleanups
2013-04-08 Added debug option
2013-04-08 README Update
2013-04-08 RST fix in readme
2013-04-08 README Update (part2)
2013-04-08 Added run all script
2013-04-08 Added an example of the time problem
2013-04-08 Added samples sorted
2013-04-09 Added gitignore for v1 schematic
2013-04-09 Now sorting on by ts or time
2013-04-09 Removed unused code
2013-04-09 ToString cleanup
2013-04-09 Update git ignore
2013-04-09 Now using immutable list for the sample arraylist
2013-04-10 Added gnuplot script
2013-04-11 Added some validation options
2013-04-16 Small refactoring on print statistics
2013-04-16 Fixed error commit
2013-04-24 Reader is now on a different class
2013-04-24 Started work on JSON reader
2013-04-26 Our test are now on a single json file
2013-04-26 Corrected a line in results
2013-04-29 Now fetching our json files
2013-04-29 Changed parameters for input file
2013-04-29 Fixed some errors associated with the new option
2013-04-29 Corrected gap validation
2013-04-29 Just some comments in kernel reader and receiver
2013-04-30 Some fixes in printing the date
2013-05-02 Moved test directory
2013-05-02 Added their results
2013-05-02 Removed an hour to compensate UTC
2013-05-20 Now removing outliers
2013-05-21 Removed previous day tests results from json file
2013-05-21 No longer using imutable lists (because now I remove outliers)
2013-05-23 Added their v2 result files
2013-05-30 Fixed the notes of the clock
2013-05-30 Small correction to last commit
2014-04-08 Added fake sender
2014-05-19 Made sure nanoseconds in timestamps come from kernel
2014-05-19 Started v3 board
2014-05-23 One more gitignore
2014-05-23 Starting to cleanup the interruption module
2014-05-26 Rewritten large chunk of code (not tested)
2014-05-26 Corrected bug
2014-05-27 Better makefile
2014-05-27 Corrected small bug and seq number is now in relation to second
    (not to packet number)
2014-05-28 Corrected time bug and network.sh auto coppied
2014-05-30 Made circular buffer fast
2014-06-02 Small change to circ buffer
2014-06-02 Change kern debug message priority
2014-06-02 SMall corrections
2014-06-08 added new EAGLE Cam job config
2014-06-13 Updated Cam file to correct some errors in Gerber file generation
2014-06-17 Temporary fix to time values
2014-06-19 Small clarification in schematic
    0.1f = 100uf
2014-06-19 Update subproject
2014-06-20 Removed some old code
2014-06-26 Add batman-adv.ko module
2014-07-01 Fixed all except IC8
2014-07-02 Keeping track of gerber files
2014-07-02 Now generating platted non platted files (with error)
2014-07-02 Gerber files all problems solved
2014-07-10 Added log when PPS is missed
2014-07-11 Corrected bug in receiver in printing timestamps
2014-07-11 Dos2unix in README and submodules init in Makefile
2014-07-11 Corrected gps_time Makefile
2014-07-11 No longer printing the PPS message
2014-07-11 Make the timestamp in miavita packet_t as unsigned
    instead of signed
2014-07-11 Debug improvements to init counter
2014-07-11 Updating ts7500_kernel commit
2014-07-11 Updating visualiation submodule
2014-07-11 Update git submodules
2014-07-17 Changed README
2014-07-17 Some cleaning
2014-07-17 Added makefile for binaries in initrd
2014-07-23 Added GPS code for handling Trimble Condor Modified init_counter to use new GPS code
2014-07-23 xuarctl adapted for Trimble Condor
    Changed serial parameters to 8n1 as this GPS module does not use parity in the serial port.
2014-07-23 Removed unused variables.
2014-07-30 Logging to sd and usb
2014-07-30 Added colors states
2014-08-01 Add rsta250.dat
2014-08-08 Forced PPS. Added GPS documentation.
    Forced the Condor GPS module to produce PPS signal regardless of previous configuration.
    Added the manuals for the condor and the lassen_iq (previously used) GPS modules.
2014-09-04 Add instructions to README
